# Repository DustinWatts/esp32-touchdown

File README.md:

# ESP32 TouchDown

## Where to buy?

Available from:

- Tindie: -> https://www.tindie.com/products/dustinwattsnl/esp32-touchdown/ (Ships from The Netherlands)

- Lectronz -> https://lectronz.com/products/esp32-touchdown (Ships from The Netherlands)

- Eplop Electornics -> https://store.eplop.co.uk/product/esp32touchdown/ (Ships from the UK)

- PCBWay -> https://www.pcbway.com/project/gifts_detail/ESP32_TouchDown.html (Ships from China) 

## FreeTouchDeck

#### Your ESP32 TouchDown comes with FreeTouchDeck pre-installed. Check out this simple start guide: [With FreeTouchDeck pre-installed](https://github.com/DustinWatts/esp32-touchdown/wiki/With-FreeTouchDeck-pre-installed)

While working on [FreeTouchDeck](https://github.com/DustinWatts/FreeTouchDeck), I really wanted to use capacitive touch. Unfortunately, most modules I could find were resistive touch and capacitive touch has a much nicer user experience. While I was designing, it made sense to put the ESP32 on the board itself, removing the need for an ESP32 Dev board. I wanted to take full advantage of the ESP32 wireless capabilities (Wifi, BLE) so I included a battery management circuit. ESP32 TouchDown can run off of a LiPo battery and also charge it. Here is a full list of the features:

- ESP32-WROOM-32D
- ILI9488 480*320 TFT screen in 4-wire SPI mode
- FT62x6 Capacitive Touch Controller
- APK2112 3.3V regulator _(On V1.1 of the board an AP7365 is used, see changelog.txt)_
- MCP73831 battery management IC _(On V1.1 of the board a Shouding SD8016 is used, see changelog.txt)_
- CP2102 USB-to-UART bridge
- USB-C connector
- microSD card holder
- Battery voltage divider connected to GPIO35
- Passive buzzer connected to GPIO26
- 12 unused GPIO's broken out
- Stemma / JST-PH I2C connector

ESP32 TouchDown works out of the box (as ESP32 Dev Module) with the Arduino IDE, providing you have installed the ESP32 Arduino Core. If you have not, this is where you can find it: [https://github.com/espressif/arduino-esp32](https://github.com/espressif/arduino-esp32).

## Documentation:

Documentation can be found in the [Wiki](https://github.com/DustinWatts/esp32-touchdown/wiki).

## TFT screen and touch controller

ESP32 TouchDown uses an 480x320 screen with an ILI9488 ([datasheet](https://github.com/DustinWatts/esp32-touchdown/blob/main/Hardware/Datasheets/ILITEK_ILI9488.pdf)) driver. There are numerous drivers out there, but I found TFT_eSPI by Bodmer the most versatile. [https://github.com/Bodmer/TFT_eSPI](https://github.com/Bodmer/TFT_eSPI). 

Pins used by the TFT screen are:

- GPIO2 -> DC_RS
- GPIO4 -> TFT_RESET
- GPIO15 -> TFT_CS
- GPIO18 -> SPI Clock
- GPIO23 -> SDI (MOSI)

The TFT backlight anode (positive supply) is selectable via a jumper on the back. You can either power it directly from 3.3V or use GPIO32. By default, the positive source is GPIO32. You can this pin and use PWM to control the backlight brightness.

_Note: On V1.1 of the board the jumpers used are with bridged pads. So by default have no solder blob. See changelog.txt_

The touch controller is a FocalTech FT62x6 ([datasheet](https://github.com/DustinWatts/esp32-touchdown/blob/main/Hardware/Datasheets/FT6236-FocalTechSystems.pdf)). The first batch uses an FT6236 and the second batch of boards has the FT6206. Both have the same I2C address of 0X38. I made an Arduino IDE library available here: [https://github.com/DustinWatts/FT6236](https://github.com/DustinWatts/FT6236). This library also supports the FT6202.

Pins used by the FT62x6 are:

- GPIO21 -> I2C data
- GPIO22 -> I2C clock
- GPIO27 -> IRQ

## GPIO Breakout

The following GPIO's are broken out on the header:

- GPIO 12
- GPIO 13
- GPIO 14
- GPIO 16
- GPIO 17
- SCK (GPIO 18, used as SPI clock)
- SDO (GPIO 19, used as SPI MOSI)
- SDA (GPIO 21, used as I2C data)
- SCL (GPIO 22, used as I2C clock)
- SDI (GPIO 23, used as SPI MISO)
- GPIO 33
- GPIO 34 (note: INPUT only!)

## SD Card

The following pins are used by the SD card holder:

- GPIO 25 --> CD/DAT3
- GPIO 23 --> CMD
- GPIO 18 --> CLK
- GPIO 19 --> DAT0

*CD (card detect) DAT1 and DAT2 are not connected.*

## Speaker (buzzer)

- GPIO 26

## Uploading code to the ESP32 TouchDown

For FreeTouchDeck installation instructions see: https://github.com/DustinWatts/FreeTouchDeck/wiki/1.-Installation

For other code: The ESP32 TouchDown uses the same configuration as an ESP32 Dev Module. So you can use those board definitions to upload your own code to the ESP32 TouchDown:

## Open Source

Everything about the ESP32 TouchDown is open source. This means I provide you will all the designs I make. In this repository, you will find the KiCad project, including schematic, and board layout. Also, the complete BOM is available to you. I have included the datasheets of all the hardware used.

<div style="margin:0 auto;">
  
  <div> 
    &nbsp;&nbsp;&nbsp;&nbsp;&nbsp;&nbsp;&nbsp;&nbsp;&nbsp;&nbsp;&nbsp;&nbsp;&nbsp;&nbsp;&nbsp;&nbsp;&nbsp;&nbsp;
    
  </div>

</div>

## Support Me

If you like what I am doing, there are a number of ways you can support me. 

| Platform | Link|
|:-----:|:-----|
|  | You can follow me on Twitter: [@dustinwattsnl](https://twitter.com/dustinwattsnl "Follow me on Twitter")|
|  | You can subscribe to my channel on Youtube: [/dustinWatts](https://www.youtube.com/dustinwatts "Subscribe to my YouTube channel") |
|  | You can support me by becoming a patron on Patreon: https://www.patreon.com/dustinwatts |
|  | You can make a one time donation using PayPal.me: https://www.paypal.me/dustinwattsnl |

## Help

For quick access to help you can join my Discord server where I have a dedicated #esp32-touchdown channel. https://discord.gg/RE3XevS

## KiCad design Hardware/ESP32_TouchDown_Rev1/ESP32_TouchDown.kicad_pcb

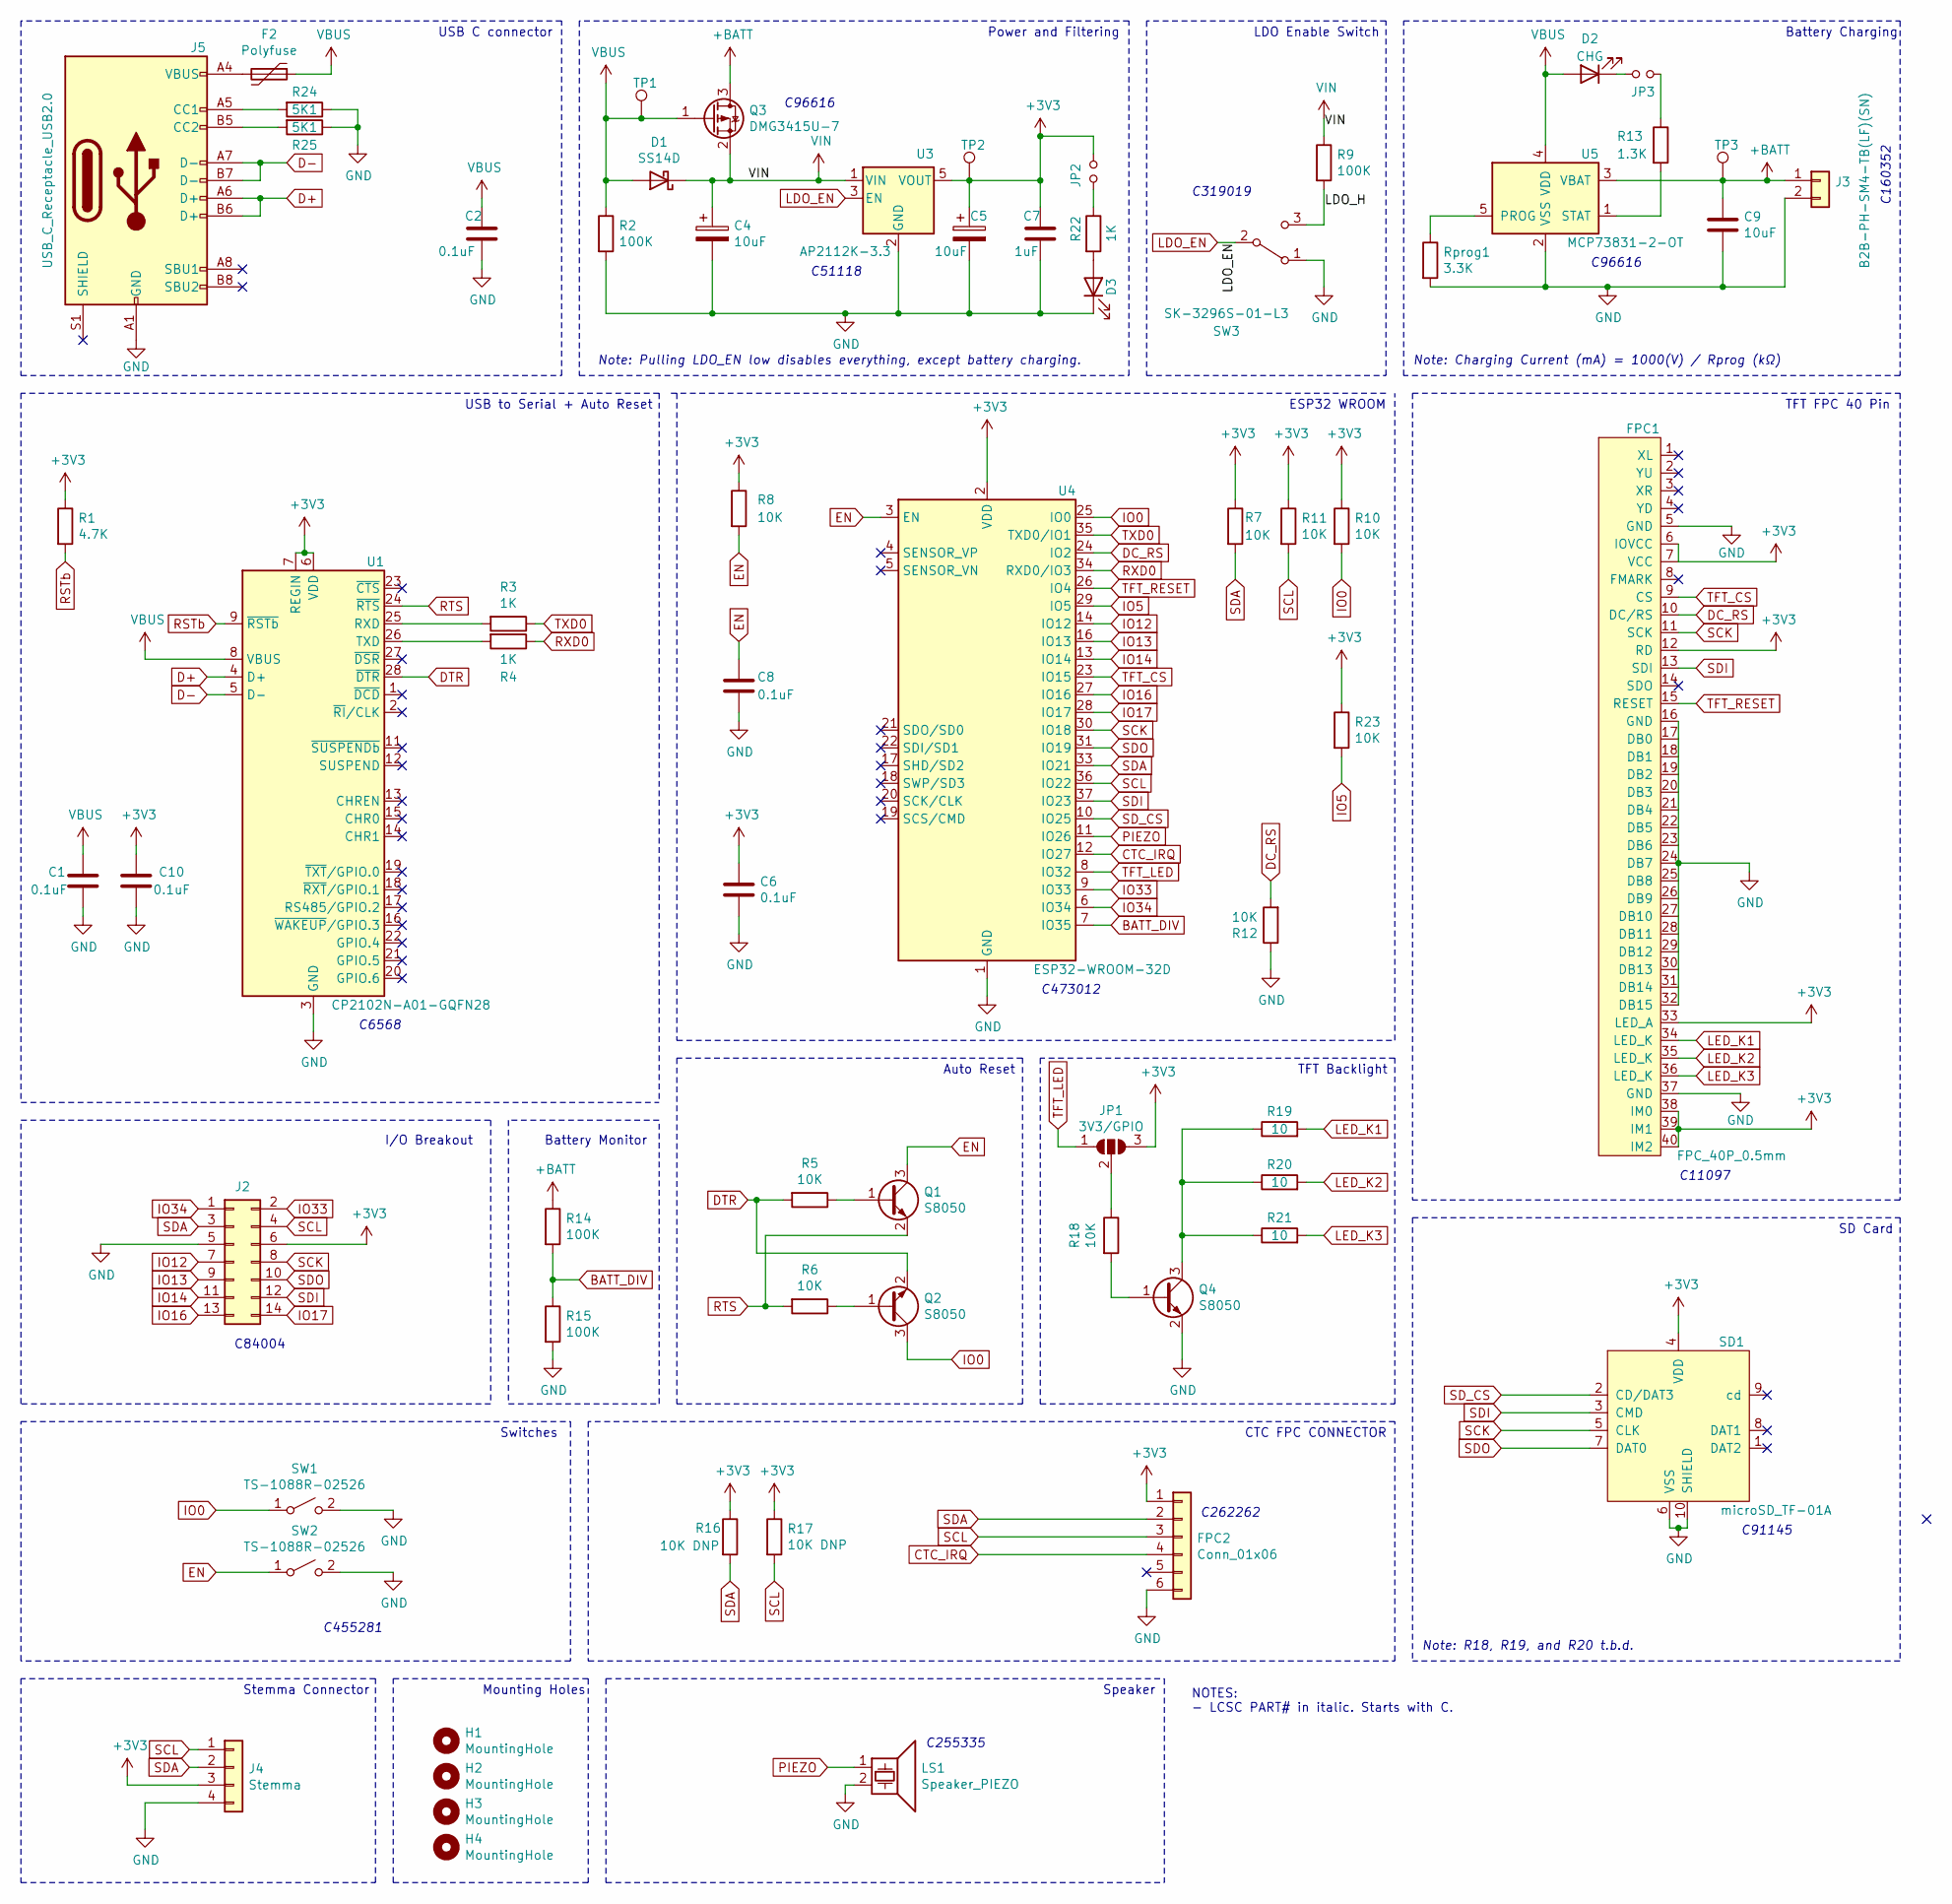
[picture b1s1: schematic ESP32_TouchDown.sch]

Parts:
C1, C2, C6, C8, C10: 0.1uF; C_0603_1608Metric
C4, C5: 10uF; CP_EIA-3216-18_Kemet-A
C7: 1uF; C_0603_1608Metric
C9: 10uF; C_0603_1608Metric
D1: SS14D; D_SMA
D2: CHG; LED_0603_1608Metric
D3: ON; LED_0603_1608Metric
F2: Polyfuse; Fuse_0805_2012Metric
FPC1: FPC_40P_0.5mm; Hirose_FH12-40S-0.5SH_1x40-1MP_P0.50mm_Horizontal
FPC2: Conn_01x06; Hirose_FH12-6S-0.5SH_1x06-1MP_P0.50mm_Horizontal
H1, H2, H3, H4: MountingHole; MountingHole_2.5mm_Pad_Via
J2: Conn_02x07_Odd_Even; PinHeader_2x07_P2.54mm_Vertical_SMD
J3: B2B-PH-SM4-TB(LF)(SN); JST_PH_B2B-PH-SM4-TB_1x02-1MP_P2.00mm_Vertical
J4: Stemma; JST_PH_S4B-PH-SM4-TB_1x04-1MP_P2.00mm_Horizontal
J5: USB_C_Receptacle_USB2.0; USB_C_Receptacle_XKB_U262-16XN-4BVC11
JP1: 3V3/GPIO; SolderJumper-3_P1.3mm_Open_RoundedPad1.0x1.5mm_NumberLabels
JP2, JP3: Jumper_NO_Small; SolderJumper-2_P1.3mm_Open_RoundedPad1.0x1.5mm
LS1: Speaker_PIEZO; INGHAi GSC1625YB-3V4000
Q1, Q2, Q4: S8050; SOT-23
Q3: DMG3415U-7; SOT-23
R1: 4.7K; R_0603_1608Metric
R2, R9, R14, R15: 100K; R_0603_1608Metric
R3, R4, R22: 1K; R_0603_1608Metric
R5, R6, R7, R8, R10, R11, R12, R18, R23: 10K; R_0603_1608Metric
R13: 1.3K; R_0603_1608Metric
R16, R17: 10K DNP; R_0603_1608Metric
R19, R20, R21: 10; R_0603_1608Metric
R24, R25: 5K1; R_0603_1608Metric
Rprog1: 3.3K; R_0603_1608Metric
SD1: microSD_TF-01A; microSD_TF-01A-C91145
SW1, SW2: TS-1088R-02526
SW3: SK-3296S-01-L3; SW_SPDT_CK-JS102011SAQN
TP1, TP2, TP3: TestPoint; TestPoint_Pad_D1.0mm
U1: CP2102N-A01-GQFN28; QFN-28-1EP_5x5mm_P0.5mm_EP3.35x3.35mm
U3: AP2112K-3.3; SOT-23-5
U4: ESP32-WROOM-32D; ESP32-WROOM-32
U5: MCP73831-2-OT; SOT-23-5

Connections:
+3V3: C5.1, C6.1, C7.1, C10.1, FPC1.6 (IOVCC), FPC1.7 (VCC), FPC1.12 (RD), FPC1.33 (LED_A), FPC1.38 (IM0), FPC1.39 (IM1), FPC1.40 (IM2), FPC2.1, J2.6, J4.3, JP1.3 (B), JP2.2, R1.1, R7.1, R8.1, R10.1, R11.1, R16.1, R17.1, R23.1, SD1.4 (VDD), TP2.1, U1.6 (VDD), U1.7 (REGIN), U3.5 (VOUT), U4.2 (VDD)
+BATT: C9.1, J3.1, Q3.3 (D), R14.1, TP3.1, U5.3 (VBAT)
/LDO_H: R9.2, SW3.3 (C)
/VIN: C4.1, D1.1 (K), Q3.2 (S), R9.1, U3.1 (VIN)
BATT_DIV: R14.2, R15.1, U4.7 (IO35)
CTC_IRQ: FPC2.4, U4.12 (IO27)
D+: J5.A6 (D+), J5.B6 (D+), U1.4 (D+)
D-: J5.A7 (D-), J5.B7 (D-), U1.5 (D-)
DC_RS: FPC1.10 (DC/RS), R12.2, U4.24 (IO2)
DTR: Q2.2 (B), R5.2, U1.28 (~DTR)
EN: C8.1, Q1.3 (C), R8.2, SW2.1 (A), U4.3 (EN)
GND: C1.2, C2.2, C4.2, C5.2, C6.2, C7.2, C8.2, C9.2, C10.2, D3.1 (K), FPC1.5 (GND), FPC1.16 (GND), FPC1.17 (DB0), FPC1.18 (DB1), FPC1.19 (DB2), FPC1.20 (DB3), FPC1.21 (DB4), FPC1.22 (DB5), FPC1.23 (DB6), FPC1.24 (DB7), FPC1.25 (DB8), FPC1.26 (DB9), FPC1.27 (DB10), FPC1.28 (DB11), FPC1.29 (DB12), FPC1.30 (DB13), FPC1.31 (DB14), FPC1.32 (DB15), FPC1.37 (GND), FPC2.6, J2.5, J3.2, J4.4, J5.A1 (GND), J5.A12 (GND), J5.B1 (GND), J5.B12 (GND), LS1.2, Q4.2 (B), R2.2, R12.1, R15.2, R24.1, R25.1, Rprog1.2, SD1.6 (VSS), SD1.10 (SHIELD), SW1.2 (B), SW2.2 (B), SW3.1 (A), U1.3 (GND), U1.29 (GND), U3.2 (GND), U4.1 (GND), U4.15 (GND), U4.38 (GND), U4.39 (GND), U5.2 (VSS)
IO0: Q2.3 (C), R10.2, SW1.1 (A), U4.25 (IO0)
IO5: R23.2, U4.29 (IO5)
IO12: J2.7, U4.14 (IO12)
IO13: J2.9, U4.16 (IO13)
IO14: J2.11, U4.13 (IO14)
IO16: J2.13, U4.27 (IO16)
IO17: J2.14, U4.28 (IO17)
IO33: J2.2, U4.9 (IO33)
IO34: J2.1, U4.6 (IO34)
LDO_EN: SW3.2 (B), U3.3 (EN)
LED_K1: FPC1.34 (LED_K), R19.2
LED_K2: FPC1.35 (LED_K), R20.2
LED_K3: FPC1.36 (LED_K), R21.2
unnamed: D2.1 (K), JP3.1
unnamed: D3.2 (A), R22.2
unnamed: F2.2, J5.A4 (VBUS), J5.A9 (VBUS), J5.B4 (VBUS), J5.B9 (VBUS)
unnamed: J5.A5 (CC1), R24.2
unnamed: J5.B5 (CC2), R25.2
unnamed: JP1.2 (C), R18.1
unnamed: JP2.1, R22.1
unnamed: JP3.2, R13.1
unnamed: Q1.1 (E), R5.1
unnamed: Q2.1 (E), R6.1
unnamed: Q4.1 (E), R18.2
unnamed: Q4.3 (C), R19.1, R20.1, R21.1
unnamed: R3.2, U1.25 (RXD)
unnamed: R4.2, U1.26 (TXD)
unnamed: R13.2, U5.1 (STAT)
unnamed: Rprog1.1, U5.5 (PROG)
PIEZO: LS1.1, U4.11 (IO26)
RSTb: R1.2, U1.9 (~RSTb)
RTS: Q1.2 (B), R6.2, U1.24 (~RTS)
RXD0: R4.1, U4.34 (RXD0/IO3)
SCK: FPC1.11 (SCK), J2.8, SD1.5 (CLK), U4.30 (IO18)
SCL: FPC2.3, J2.4, J4.1, R11.2, R17.2, U4.36 (IO22)
SDA: FPC2.2, J2.3, J4.2, R7.2, R16.2, U4.33 (IO21)
SDI: FPC1.13 (SDI), J2.12, SD1.3 (CMD), U4.37 (IO23)
SDO: J2.10, SD1.7 (DAT0), U4.31 (IO19)
SD_CS: SD1.2 (CD/DAT3), U4.10 (IO25)
TFT_CS: FPC1.9 (CS), U4.23 (IO15)
TFT_LED: JP1.1 (A), U4.8 (IO32)
TFT_RESET: FPC1.15 (RESET), U4.26 (IO4)
TXD0: R3.1, U4.35 (TXD0/IO1)
VBUS: C1.1, C2.1, D1.2 (A), D2.2 (A), F2.1, Q3.1 (G), R2.1, TP1.1, U1.8 (VBUS), U5.4 (VDD)

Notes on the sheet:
Power and Filtering
LDO Enable Switch
Battery Charging
Battery Monitor
ESP32 WROOM
TFT FPC 40 Pin
Note: Pulling LDO_EN low disables everything, except battery charging.
Note: Charging Current (mA) = 1000(V) / Rprog (kΩ)
CTC FPC CONNECTOR
Speaker
Switches
I/O Breakout
C255335
NOTES: - LCSC PART# in italic. Starts with C.
Mounting Holes
SD Card
Stemma Connector
C262262
C473012
C96616
C91145
Note: R18, R19, and R20 t.b.d.
C51118
C319019
C160352
C11097
C455281
Auto Reset
C6568
USB to Serial + Auto Reset
TFT Backlight
C84004
USB C connector

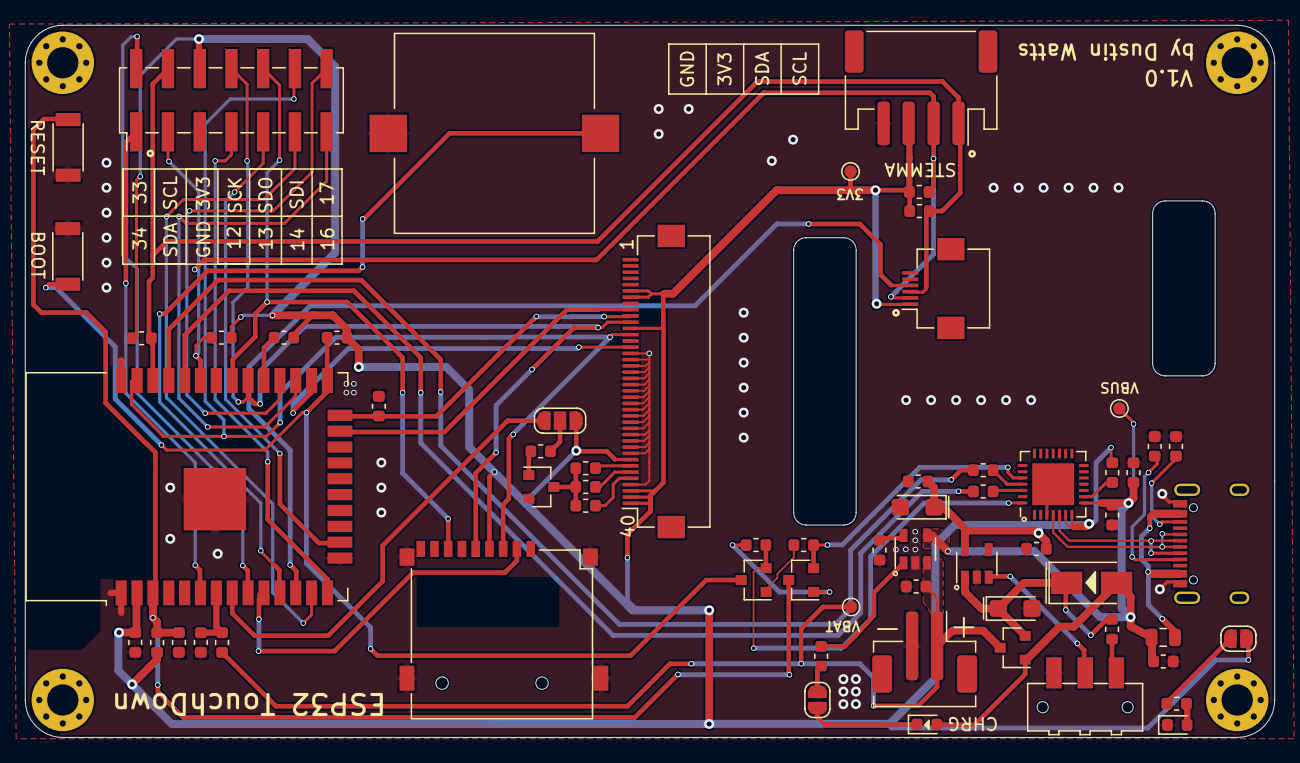
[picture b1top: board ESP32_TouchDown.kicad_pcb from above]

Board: 2 copper layers, 100.0 x 57.0 mm, 68 parts (0 on the bottom side), 56 nets.

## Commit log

2020-11-19 Update to latest
2020-12-11 Revision 1
2021-01-01 Revision 1
    Updated schematic with LCSC part numbers and added extra examples.
2021-01-01 Revision 1
    Update schematic PDF filename.
2021-01-01 Revision 1
    Update KICAD project.
2021-01-04 Update Examples
    Added two examples: a keypad demo and a secure HA connection demo.
2021-01-05 Update Examples
    Updated some of the examples to include reference to TFT_eSPI. Also included a TFT_eSPI User_Setup.h
2021-01-15 Added Keyboard Example
    New example: Keyboard.
2021-01-26 Update Examples
    Updated comments to include which libraries need to be installed.
2021-01-28 Created Case .stl files
2021-01-30 Added 30° angle FTD style back
2021-01-30 Add 30° angled FTD back rendering
2021-01-30 Spelling
2021-01-30 File name
2021-02-15 Minor spelling and punctuation fixes
2021-02-16 whoops missed a spelling misstake.
    😨
2021-02-16 Update with new images and updated BOM
2021-02-17 Update README.md
    couple of minor spelling and grammar fixes
2021-02-28 add wallmount for battery
2021-03-17 Added 3D model
    Added .f3d, .obj and .step.
2021-05-20 Updated 3D models
    The height of the TFT screen was incorrect. Was 3.1mm, should be 4.1mm.
2021-07-13 Update README.md
    Added Thingiverse cases.
2021-09-10 Added ArduinoOSC example
    An example showing how to use ArduinoOSC to display cues on the ESP32 TouchDown.
2022-04-20 Update README.md
    Added badges
2022-05-06 Hardware Rev1.1
    Added KiCad project, schematics, board and gerbers for Rev1.1, see changelog
2022-05-08 Added V1.1 Datasheets, update BOM
    Updated the BOM with alternate parts. Some of them used on V1.1. Also added the datasheets for those parts.
2022-05-08 Update README.md
    Default of the backlight is GPIO32, changed this in the README.md
2022-05-29 Remove Pre-Loaded_Sketch
    The Pre-Loaded_Sketch is deprecated because all ESP32 TouchDowns come pre-loaded with FreeTouchDeck.
2022-05-29 Upated README.md
    Replaced the picture with the welcome sketch with one from Tindie.
2022-05-29 Add changelog.txt, update README.md
    Added changelog.txt describing changes since the board version is now V1.1. Also updated the README.md with changes from the changelog.
2022-05-31 Upload new image
2022-05-31 Uploaded new image
2023-02-14 Just some housekeeping
    Removed boards.txt (this was nonsense) and renamed `changelog.txt` changelog V1 to V1.1`.
2023-02-14 Update places to buy
    The ESP32 TouchDown is also available from lectronz.com
2023-03-09 Added .f3z file
    For modifying the case in Fusion360.
2023-04-18 Removed #define TFT_BACKLIGHT_ON HIGH
    This interferes with backlight dimming.
2023-10-01 Added Grid Front for Case
    Added Grid Front for Case.
2023-10-01 Update README.md
    Small correction.
2023-10-03 Reworked the case grid
2023-10-20 Update README.md
    Add speaker pinout.
2024-04-20 Update Backlight HIGH by default
